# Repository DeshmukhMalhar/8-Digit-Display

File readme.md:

A 8 digit display using 7 segment displays and 2 74HC595 s

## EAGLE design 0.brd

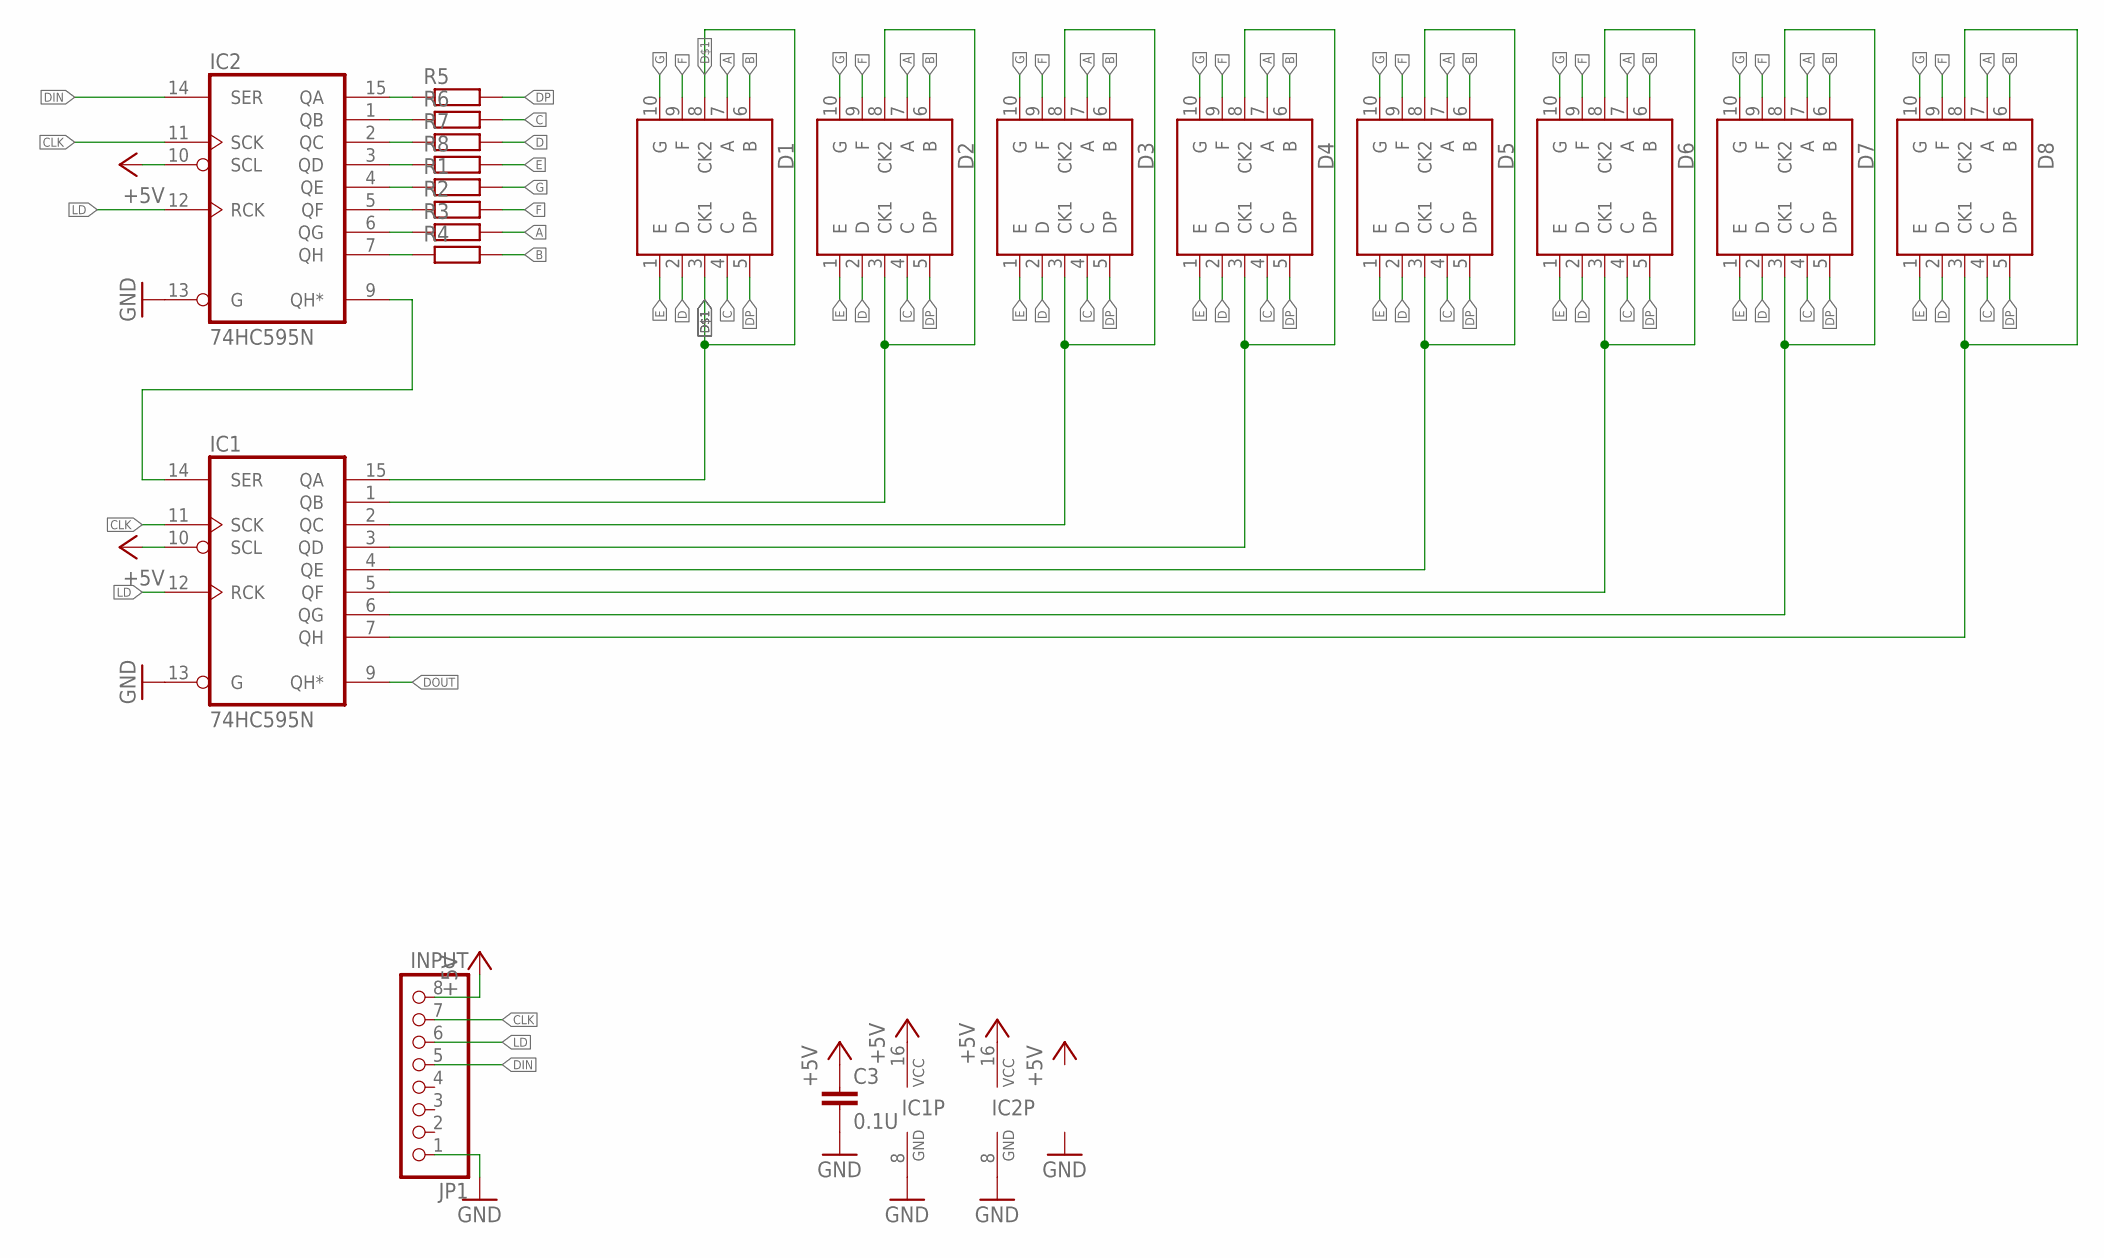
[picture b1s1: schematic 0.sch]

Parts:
C3: 0.1U; C050-024X044
D1, D2, D3, D4, D5, D6, D7, D8: 7SEG-CK; 7SEG-13
IC1, IC2: 74HC595N; DIL16
JP1: INPUT; 1X08
R1, R2, R3, R4, R5, R6, R7, R8: R-EU_0207/7; 0207/7

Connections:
+5V: C3.1, IC1.10 (SCL), IC1.16 (VCC), IC2.10 (SCL), IC2.16 (VCC), JP1.8
A: D1.7 (A), D2.7 (A), D3.7 (A), D4.7 (A), D5.7 (A), D6.7 (A), D7.7 (A), D8.7 (A), R3.2
B: D1.6 (B), D2.6 (B), D3.6 (B), D4.6 (B), D5.6 (B), D6.6 (B), D7.6 (B), D8.6 (B), R4.2
C: D1.4 (C), D2.4 (C), D3.4 (C), D4.4 (C), D5.4 (C), D6.4 (C), D7.4 (C), D8.4 (C), R6.2
CLK: IC1.11 (SCK), IC2.11 (SCK), JP1.7
D: D1.2 (D), D2.2 (D), D3.2 (D), D4.2 (D), D5.2 (D), D6.2 (D), D7.2 (D), D8.2 (D), R7.2
D$1: D1.3 (CK1), D1.8 (CK2), IC1.15 (QA)
DIN: IC2.14 (SER), JP1.5
DOUT: IC1.9 (QH*)
DP: D1.5 (DP), D2.5 (DP), D3.5 (DP), D4.5 (DP), D5.5 (DP), D6.5 (DP), D7.5 (DP), D8.5 (DP), R5.2
E: D1.1 (E), D2.1 (E), D3.1 (E), D4.1 (E), D5.1 (E), D6.1 (E), D7.1 (E), D8.1 (E), R8.2
F: D1.9 (F), D2.9 (F), D3.9 (F), D4.9 (F), D5.9 (F), D6.9 (F), D7.9 (F), D8.9 (F), R2.2
G: D1.10 (G), D2.10 (G), D3.10 (G), D4.10 (G), D5.10 (G), D6.10 (G), D7.10 (G), D8.10 (G), R1.2
GND: C3.2, IC1.8 (GND), IC1.13 (G), IC2.8 (GND), IC2.13 (G), JP1.1
LD: IC1.12 (RCK), IC2.12 (RCK), JP1.6
unnamed: IC2.15 (QA), R5.1
unnamed: IC2.1 (QB), R6.1
unnamed: IC2.2 (QC), R7.1
unnamed: IC2.3 (QD), R8.1
unnamed: IC2.4 (QE), R1.1
unnamed: IC2.5 (QF), R2.1
unnamed: IC2.6 (QG), R3.1
unnamed: IC2.7 (QH), R4.1
unnamed: IC1.14 (SER), IC2.9 (QH*)
unnamed: D2.3 (CK1), D2.8 (CK2), IC1.1 (QB)
unnamed: D3.3 (CK1), D3.8 (CK2), IC1.2 (QC)
unnamed: D5.3 (CK1), D5.8 (CK2), IC1.4 (QE)
unnamed: D6.3 (CK1), D6.8 (CK2), IC1.5 (QF)
unnamed: D7.3 (CK1), D7.8 (CK2), IC1.6 (QG)
unnamed: D8.3 (CK1), D8.8 (CK2), IC1.7 (QH)
unnamed: D4.3 (CK1), D4.8 (CK2), IC1.3 (QD)

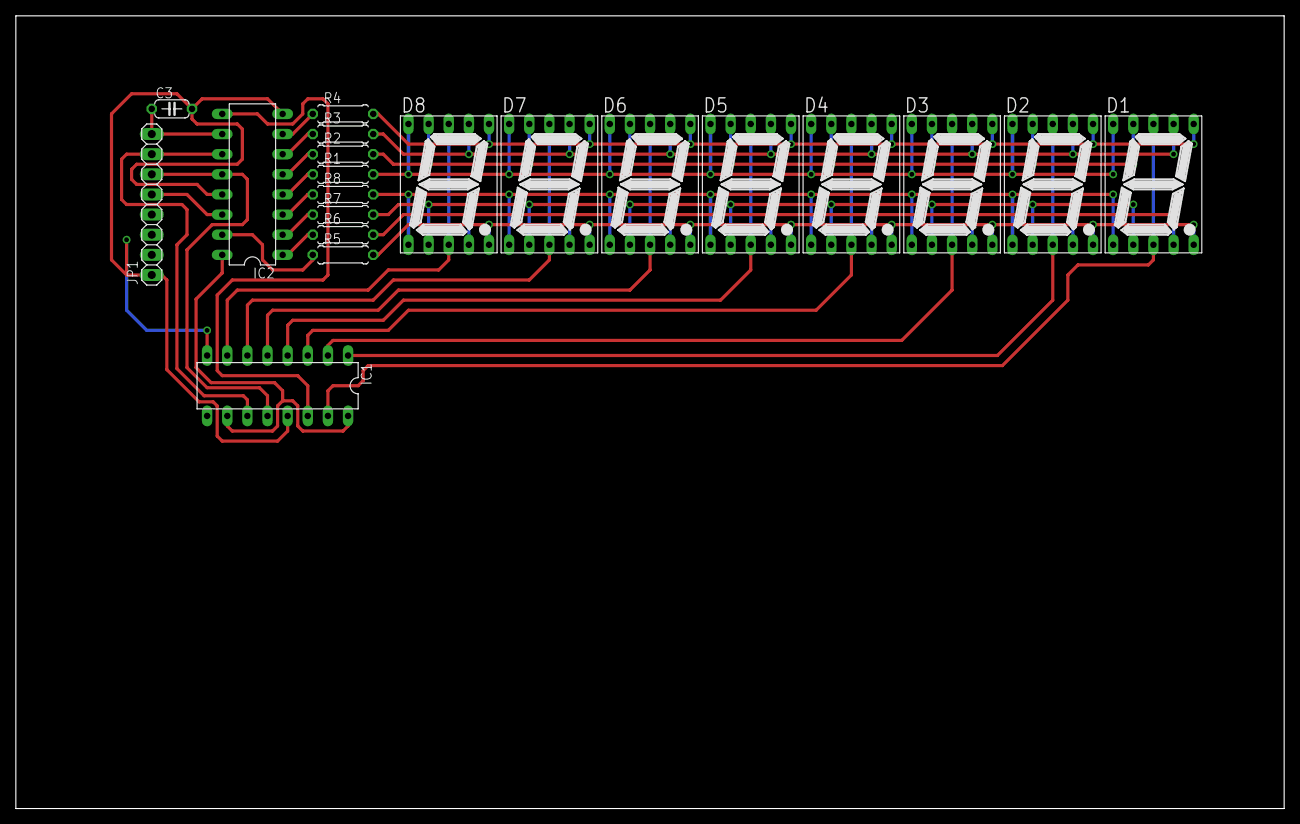
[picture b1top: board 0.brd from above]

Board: 2 copper layers, 160.0 x 100.0 mm, 20 parts (0 on the bottom side), 30 nets.

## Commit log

2017-08-26 First edition of 7seg display
2017-08-26 Added a readme
